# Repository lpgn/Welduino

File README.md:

# Welduino
 This is an atempt to create a controller for my ESAB MIG welder LKA150

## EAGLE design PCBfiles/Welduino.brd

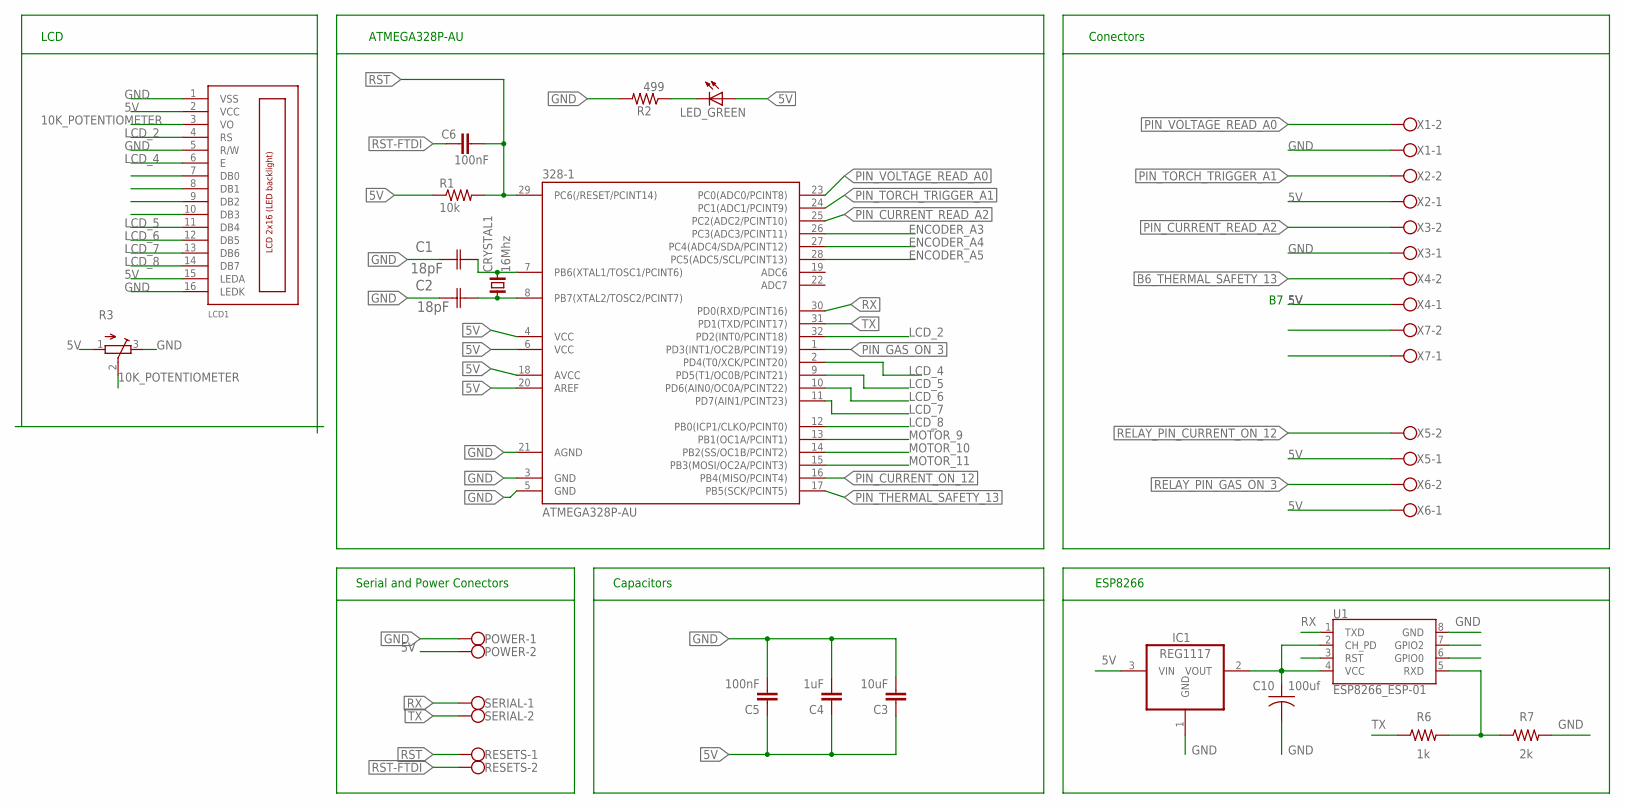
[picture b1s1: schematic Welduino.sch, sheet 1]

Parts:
328-1: ATMEGA328P-AU; TQFP32-08
C1, C2: 18pF; CAPC3216X178N
C3: 10uF; 1206
C4: 1uF; 1206
C5, C6: 100nF; 1206
C10: 100uf; C1206FAB
CRYSTAL1: 16Mhz; 2-SMD-5X3
IC1: REG1117; SOT223
LCD1: LCD_2X16_SIL; HY-1602F
LED_GREEN: LED1206; 1206
POWER: W237-102
R1: 10k; 1206
R2: 499; 1206
R3: TRIM_EU-3223J; 3223J
R6: 1k; R1206FAB
R7: 2k; R1206FAB
RESETS: W237-102
SERIAL: W237-102
U1: ESP8266_ESP-01
X1, X2, X3, X4, X5, X6, X7: W237-102

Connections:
5V: 328-1.4 (VCC), 328-1.6 (VCC), 328-1.18 (AVCC), 328-1.20 (AREF), C3.1, C4.1, C5.1, IC1.3 (VIN), LCD1.2 (VCC), LCD1.15 (LEDA), LED_GREEN.1 (A), POWER.2, R1.1, R3.1 (A), X2.1, X4.1, X5.1, X6.1
10K_POTENTIOMETER: LCD1.3 (VO), R3.2 (S)
B6_THERMAL_SAFETY_13: X4.2
ENCODER_A3: 328-1.26 (PC3(ADC3/PCINT11))
ENCODER_A4: 328-1.27 (PC4(ADC4/SDA/PCINT12))
ENCODER_A5: 328-1.28 (PC5(ADC5/SCL/PCINT13))
GND: 328-1.3 (GND), 328-1.5 (GND), 328-1.21 (AGND), C1.1 (C1), C2.1 (C1), C3.2, C4.2, C5.2, C10.2, IC1.1 (GND), LCD1.1 (VSS), LCD1.5 (R/W), LCD1.16 (LEDK), POWER.1, R2.2, R3.3 (E), R7.2, U1.8 (GND), X1.1, X3.1
LCD_2: 328-1.32 (PD2(INT0/PCINT18)), LCD1.4 (RS)
LCD_4: 328-1.2 (PD4(T0/XCK/PCINT20)), LCD1.6 (E)
LCD_5: 328-1.9 (PD5(T1/OC0B/PCINT21)), LCD1.11 (DB4)
LCD_6: 328-1.10 (PD6(AIN0/OC0A/PCINT22)), LCD1.12 (DB5)
LCD_7: 328-1.11 (PD7(AIN1/PCINT23)), LCD1.13 (DB6)
LCD_8: 328-1.12 (PB0(ICP1/CLKO/PCINT0)), LCD1.14 (DB7)
MOTOR_9: 328-1.13 (PB1(OC1A/PCINT1))
MOTOR_10: 328-1.14 (PB2(SS/OC1B/PCINT2))
MOTOR_11: 328-1.15 (PB3(MOSI/OC2A/PCINT3))
unnamed: 328-1.7 (PB6(XTAL1/TOSC1/PCINT6)), C1.2 (C2), CRYSTAL1.2
unnamed: R6.2, R7.1, U1.5 (RXD)
unnamed: C10.1, IC1.2 (VOUT), U1.2 (CH_PD), U1.4 (VCC)
unnamed: 328-1.8 (PB7(XTAL2/TOSC2/PCINT7)), C2.2 (C2), CRYSTAL1.1
unnamed: LED_GREEN.2 (C), R2.1
PIN_CURRENT_ON_12: 328-1.16 (PB4(MISO/PCINT4))
PIN_CURRENT_READ_A2: 328-1.25 (PC2(ADC2/PCINT10)), X3.2
PIN_GAS_ON_3: 328-1.1 (PD3(INT1/OC2B/PCINT19))
PIN_THERMAL_SAFETY_13: 328-1.17 (PB5(SCK/PCINT5))
PIN_TORCH_TRIGGER_A1: 328-1.24 (PC1(ADC1/PCINT9)), X2.2
PIN_VOLTAGE_READ_A0: 328-1.23 (PC0(ADC0/PCINT8)), X1.2
RELAY_PIN_CURRENT_ON_12: X5.2
RELAY_PIN_GAS_ON_3: X6.2
RST: 328-1.29 (PC6(/RESET/PCINT14)), C6.1, R1.2, RESETS.1
RST-FTDI: C6.2, RESETS.2
RX: 328-1.30 (PD0(RXD/PCINT16)), SERIAL.1, U1.1 (TXD)
TX: 328-1.31 (PD1(TXD/PCINT17)), R6.1, SERIAL.2

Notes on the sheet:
Serial and Power Conectors
Capacitors
ESP8266
Conectors
ATMEGA328P-AU
LCD

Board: 2 copper layers, 28 parts (1 on the bottom side), 21 nets, no tracks yet.

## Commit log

2021-01-24 add directory structure

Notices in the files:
parts and their libraries:
01_SparkFun: Licensing: CC v3.0 Share-Alike You are welcome to use this library for commercial purposes.
SparkFun-RF: Licensing: Creative Commons ShareAlike 4.0 International - https://creativecommons.org/licenses/by-sa/4.0
